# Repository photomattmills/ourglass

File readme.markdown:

# Ourglass

This is the code and design files for Ourglass, an open source watch. Feel free to use, modify, and extend in any way you see fit, all are released under the MIT license. http://ourglass.watch for updates.

# Contributing

Comments, questions, and pull requests welcome. This project follows a code of conduct (fully at code_of_conduct.md) and by contributing, you agree to abide by that code.

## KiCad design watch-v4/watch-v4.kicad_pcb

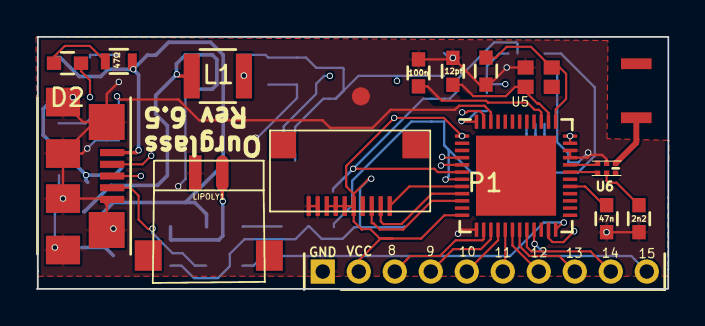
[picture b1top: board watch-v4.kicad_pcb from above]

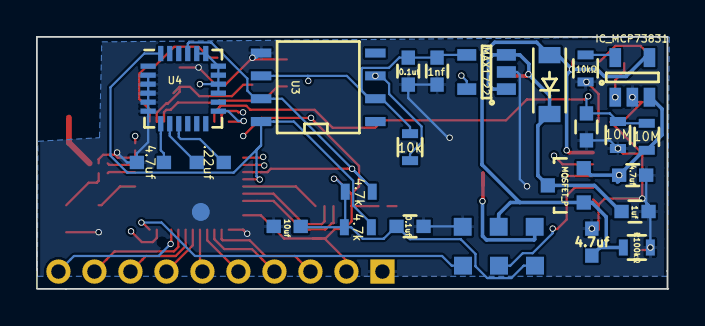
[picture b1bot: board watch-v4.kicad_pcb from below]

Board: 4 copper layers, 35.1 x 14.0 mm, 40 parts (24 on the bottom side), 40 nets.

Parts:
ANT1: -; antenna
C1: 1uf; C_0603
C2, C3, C6: 4.7uf; C_0603
C4: 100n; C_0603
C5: .22uf; C_0603
C7: 10uf; C_0603
C8, C13: 0.1uf; C_0603
C9: 47n; C_0603
C10, C15: 12pf; C_0603
C11: 2n2; C_0603
C12: 1u; C_0603
C14: 1nf; C_0603
D1: DIODESCH; SOD-123
D2: LED; C_0603
J1: CONN_10; omron_XF2M-1015-1A-2
L1: 10uH; R_1210
LIPOLY1: BATTERY; JST_2_pos
P1: Expansion Header; Pin_Header_Straight_1x10_Pitch2.00mm
P2: Test Points; test_points
Q1: MOSFET_P; SOT-23
R1: 47Ω; R_0603
R2: 10kΩ; R_0603
R3: R100kΩ; R_0603
R4: 10k; R_0603
R5, R6: 4.7k; R_0603
R7, R8: 10M; R_0603
U1: IC_MCP73831; SOT-23-5
U2: MAX1722; SOT-23-5
U3: DS3231; SOIC-8-N
U4: LSM9DS0; QFN-24-NO-CENTER4x4mm_Pitch0.5mm
U5: NRF51822; UQFN-48-1EP_6x6mm_Pitch0.4mm
U6: BALUN; BALUN-6
X1: 16mhz; SMD-Crystal
XL1: USB_MICRO_B; USB_Micro-B

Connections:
/Accel_INT: U4.13, U5.48
/Bal1: U5.31, U6.4
/Bal2: U5.32, U6.3
/BatterySense: C12.1, R7.2, R8.1, U5.46
/ClockINT: R4.2, U3.3, U5.47
/Display_MOSI: J1.2, U5.9
/Display_SCK: J1.3, U5.10
/Display_SS: J1.1, U5.8
/EX8: P1.3, U5.14
/EX9: P1.4, U5.15
/EX10: P1.5, U5.16
/EX11: P1.6, U5.17
/EX12: P1.7, U5.18
/EX13: P1.8, U5.19
/EX14: P1.9, U5.20
/EX15: P1.10, U5.21
/EXTVCC: C2.1, D1.1, P2.5, Q1.1, R1.2, R3.1, U1.4, XL1.1
/RX: U5.5, XL1.3
/Regulator_In: C1.1, D1.2, L1.1, Q1.3, U2.1, U2.3
/Reset: P2.2, U5.23, XL1.4
/SCL: R5.1, U3.7, U4.21, U5.6
/SDA: R6.1, U3.8, U4.24, U5.7
/SWDCLK: P2.3, U5.24
/TX: U5.4, XL1.2
/VBAT: C3.1, LIPOLY1.2, P2.4, Q1.2, R7.1, U1.3
/VCC: C7.1, C8.1, C13.2, C14.2, J1.5, J1.6, J1.7, J1.8, P1.2, P2.1, R4.1, R5.2, R6.2, U2.4, U3.2, U3.6, U4.15, U4.16, U4.17, U4.18, U4.19, U4.20, U5.1, U5.12, U5.35, U5.36
/XC1: C10.1, U5.38, X1.3
/XC2: C15.1, U5.37, X1.1
GND: C1.2, C2.2, C3.2, C4.2, C6.2, C7.2, C8.2, C9.2, C10.2, C11.2, C12.2, C13.1, C14.1, C15.2, J1.9, J1.10, LIPOLY1.1, P1.1, P2.6, R2.2, R3.2, R8.2, U1.2, U2.2, U3.5, U4.2, U4.3, U4.4, U4.5, U4.6, U5.13, U5.33, U5.34, U6.2, X1.2, XL1.5
unnamed: ANT1.1, U6.1
unnamed: C4.1, U5.39
unnamed: C5.1, U4.9
unnamed: C5.2, U4.8
unnamed: C6.1, U4.7
unnamed: C9.1, U5.29
unnamed: C11.1, U6.5
unnamed: D2.1, U1.1
unnamed: D2.2, R1.1
unnamed: L1.2, U2.5
unnamed: R2.1, U1.5

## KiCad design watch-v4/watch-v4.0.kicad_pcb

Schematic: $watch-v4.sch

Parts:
12pf1: C9; C_0402
ANT1: -; antenna
C1, C6: 4.7uf; C_0402
C5: .22uf; C_0402
C7: 10uf; C_0402
C8, C13, C14: 0.1uf; C_0402
C10: 12pf; C_0402
C12: 2.2nf; C_0402
D1: DIODESCH; Diode-SMA_Standard
D2: LED; LED-0603
J1: CONN_10; omron_XF2M-1015-1A
L1: 10uH; R_1210
LIPOLY1: BATTERY; Pin_Header_Straight_1x02
P1: array connection; Pin_Header_Straight_1x02
Q1: MOSFET_P; SOT-23
R1: 47Ω; R_0402
R2: 10kΩ; R_0402
R3: R10kΩ; R_0402
R5, R6: 4.7k; R_0402
SW1, SW2, SW3: SPST; panasonic-evpav-switch
U1: IC_MCP73831; SOT-23-5
U2: MAX1724; SOT-23-5
U3: DS3231; SOIC-8-N
U4: LSM9DS0; QFN-24-NO-CENTER4x4mm_Pitch0.5mm
U5: NRF51822; UQFN-48-1EP_6x6mm_Pitch0.4mm
U6: BALUN
X1: 16mhz; SMD-Crystal
XL1: USB_MICRO_B; USB_Micro-B

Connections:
/RX: U5.5 (P0.01), XL1.2
/Regulator_In: D1.2 (K), L1.1, Q1.3 (S), U2.1, U2.3
/Reset: U5.23 (SWDIO/nRESET), XL1.4
/STAT: D2.2 (A), U1.1 (STAT)
/TX: U5.4 (P0.00), XL1.3
DISPLAY_MOSI: J1.2, U5.9 (P0.05)
DISPLAY_SCK: J1.1, U5.10 (P0.06)
DISPLAY_SS: J1.3, U5.8 (P0.04)
GND: 12pf1.1, C1.2, C6.2, C7.2, C8.2, C10.2, C12.2, C13.1, C14.1, J1.9, J1.10, LIPOLY1.1 (-), P1.2, R2.2, R3.2, U1.2 (VSS), U2.2, U3.5 (GND), U4.2 (RSVD2), U4.3 (RSVD3), U4.4 (RSVD4), U4.5 (GND), U4.6 (GND), U5.13 (VSS), U5.33 (VSS), U5.34 (VSS), U6.4 (bal_2), X1.2, XL1.5
unnamed: 12pf1.2, U5.37 (XC2), X1.1
unnamed: ANT1.1, U6.5 (GND)
unnamed: C5.1, U4.9 (SETP_XM)
unnamed: C5.2, U4.8 (SETC_XM)
unnamed: C6.1, U4.7 (C1_XM)
unnamed: C10.1, U5.38 (XC1), X1.3
unnamed: C12.1, U5.30 (VDD_PA), U6.3 (balanced_1)
unnamed: D2.1 (K), R1.1
unnamed: L1.2, U2.5
unnamed: C1.1, LIPOLY1.2 (+), Q1.2 (D), U1.3 (BAT)
unnamed: R2.1, U1.5 (PROG)
unnamed: SW1.2, U5.14 (P0.08)
unnamed: SW2.2, U5.15 (P0.09)
unnamed: SW3.2, U5.16 (P0.10)
unnamed: U5.31 (ANT1), U6.2 (GND)
unnamed: U5.32 (ANT2), U6.1 (ANT_OUT)
SCL: R6.1, U3.8 (SCL), U4.21 (SCL/SPC), U5.6 (P0.02)
SDA: R5.1, U3.7 (SDA), U4.24 (SDA), U5.7 (P0.03)
VCC: C7.1, C8.1, C13.2, C14.2, J1.4, J1.5, J1.6, J1.7, J1.8, R5.2, R6.2, SW1.1, SW2.1, SW3.1, U2.4, U3.2 (Vcc), U3.6 (Vbat), U4.15 (VDD), U4.16 (VDD), U4.17 (VDD), U4.18 (VDD_IO), U4.19 (CS_G), U4.20 (CS_XM), U5.1 (VDD), U5.12 (VDD), U5.35 (AVDD), U5.36 (AVDD)

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
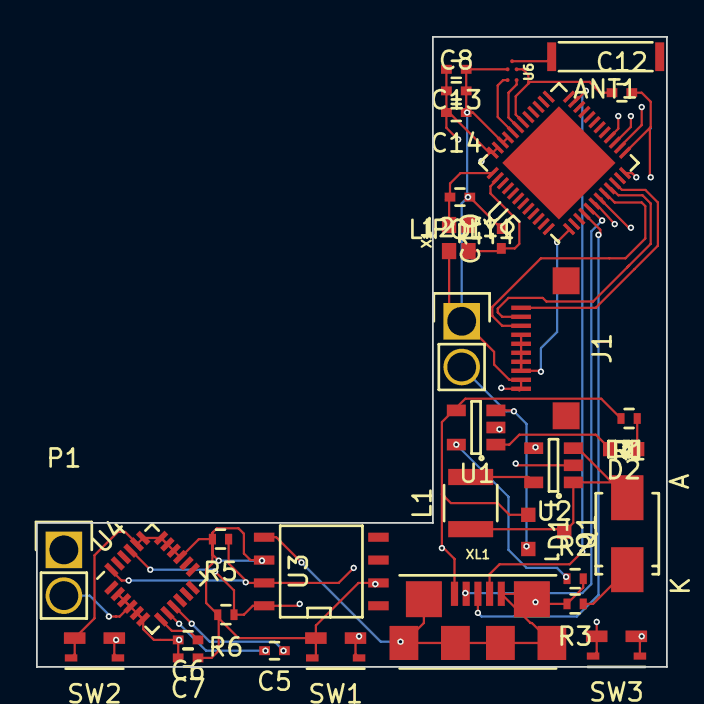
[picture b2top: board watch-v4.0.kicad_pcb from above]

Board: 4 copper layers, 35.0 x 35.0 mm, 33 parts (0 on the bottom side), 29 nets.

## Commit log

2015-06-15 add all the files for the board design
2015-06-15 add readme and license.txt
2015-06-20 move files for arduino IDE and add code of conduct
2015-06-22 board errata, new gerber files
2015-06-23 change display footprint, move filter cap to feasible location
2015-06-27 escape from git hell
2015-07-21 schematic cleanup, board work
2015-07-22 re-route board, redraw power supply in schematic
2015-07-23 forgot to netlist the new parts; now with more caps, connections
2015-10-27 really should have commited this months ago...
2015-12-14 add 4.5 gerbers
2015-12-14 re-add watch hw files
2015-12-14 update readme to reflect non-wip status
2016-04-12 up to version 5.2
2016-04-13 add pretty picture to readme
2016-05-22 save v5.2
2016-10-14 save schematic changes for 5.4
2016-10-14 v6 schematic updates
    * add expansion header
    * remove buttons
    * fix radio decoupling, gnd connections
    * change backlight to mosfet/standard leds
    * add battery connection through voltage divider
    * clock INT pullup on schematic now
2016-10-14 cleanup
2016-10-14 get rid of the global labels, tidy things up a bit
2016-10-14 more cleanup
2016-10-17 further v6 work; incomplete
2016-10-18 further traces routed, still more work to go
2016-10-20 top layer components mostly routed
2016-10-24 routed all the things
2016-11-30 v6 as sent to fab (errors!)
2017-01-31 v6.5
2017-01-31 update avr_watch with the current sketch with battery meter
2017-01-31 reorganize
2017-03-17 update board image in readme
2017-03-17 rename readme
2017-03-17 add image of board back
2017-04-05 modify to work on the smaller display
2017-04-05 switch out the regulator
